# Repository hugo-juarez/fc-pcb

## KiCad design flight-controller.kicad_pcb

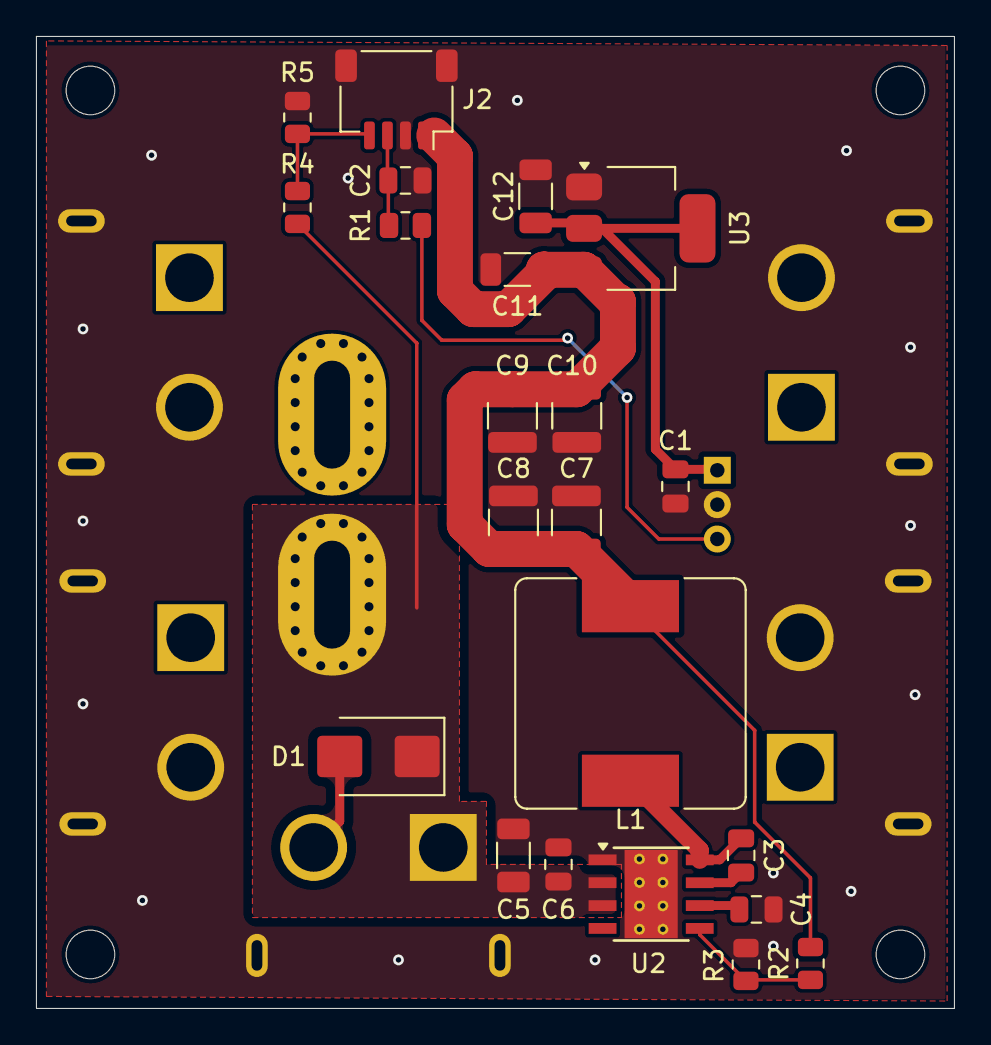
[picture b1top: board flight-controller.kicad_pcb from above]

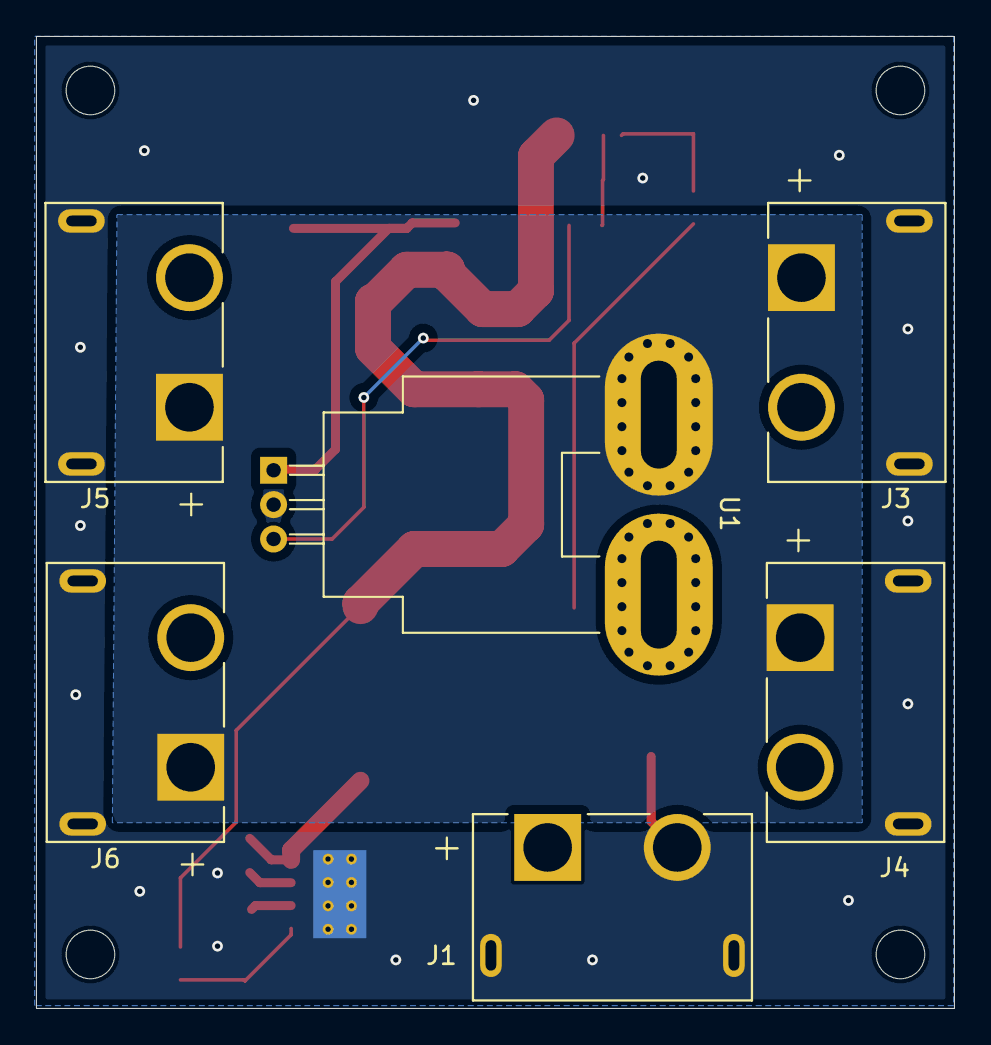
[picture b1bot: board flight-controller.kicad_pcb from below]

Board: 2 copper layers, 51.0 x 54.0 mm, 28 parts (6 on the bottom side), 12 nets.

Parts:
C1, C3: 100nF; C_0805_2012Metric
C2: 10nF; C_0805_2012Metric
C4: 1uF; C_0805_2012Metric
C5, C11, C12: 10uF; C_1206_3216Metric
C6: 220nF; C_0805_2012Metric
C7, C8, C9, C10: 22uF; C_1210_3225Metric
D1: SMBJ18A; D_SMB
J1: XT60PW-M; AMASS_XT60PW-M
J2: SM04B-SRSS-TB; JST_SH_SM04B-SRSS-TB_1x04-1MP_P1.00mm_Horizontal
J3, J4, J5, J6: XT60PW-F; AMASS_XT60PW-F
L1: SRR1260-8R2Y; L_Bourns_SRR1260
R1: 1kΩ; R_0805_2012Metric
R2: 100kΩ; R_0805_2012Metric
R3: 24.9kΩ; R_0805_2012Metric
R4: 10kΩ; R_0805_2012Metric
R5: 2.2kΩ; R_0805_2012Metric
U1: ACS773LCB-100B-PFF; Allegro_CB_PFF
U2: LMR33630ADDA; Texas_HSOP-8-1EP_3.9x4.9mm_P1.27mm_ThermalVias
U3: AMS1117-3.3; SOT-223-3_TabPin2

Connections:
+3.3V: C1.1, C12.1, U1.1 (VCC), U3.2 (VO)
+5V: C7.1, C8.1, C9.1, C10.1, C11.1, J2.1, L1.2, R2.1, U3.3 (VI)
/CURR_SENSE: C2.1, J2.3, R1.1
/VBAT: C5.1, C6.1, D1.1 (K), J1.1, R4.1, U1.4 (IP+), U2.2 (VIN), U2.3 (EN)
/VBAT_SENSE: J2.4, R4.2, R5.1
/VBAT_SW: J3.1, J4.1, J5.1, J6.1, U1.5 (IP-)
GND: C1.2, C2.2, C4.2, C5.2, C6.2, C7.2, C8.2, C9.2, C10.2, C11.2, C12.2, D1.2 (A), J1.2 (N), J1.SH1 (SHIELD), J1.SH2 (SHIELD), J2.2, J2.MP, J3.2 (N), J3.SH1 (SHIELD), J3.SH2 (SHIELD), J4.2 (N), J4.SH1 (SHIELD), J4.SH2 (SHIELD), J5.2 (N), J5.SH1 (SHIELD), J5.SH2 (SHIELD), J6.2 (N), J6.SH1 (SHIELD), J6.SH2 (SHIELD), R3.2, R5.2, U1.2 (GND), U2.1 (GND), U2.9 (GND), U3.1 (GND)
unnamed: R1.2, U1.3 (VIOUT)
unnamed: C3.1, U2.7 (BOOT)
unnamed: R2.2, R3.1, U2.5 (FB)
unnamed: C3.2, L1.1, U2.8 (SW)
unnamed: C4.1, U2.6 (VCC)

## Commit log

2026-03-22 chore: Initialize pcb project with BMI088 symbol
2026-03-22 chore: Modified to remove auto saved files
2026-03-22 feat: Added stm32 header connectors
2026-03-29 feat: Added bmp390 schematic
2026-03-29 fix: Fixed CSB pin style to inverted
2026-03-30 feat: Added bmp390 to main schematic
2026-03-30 feat: Added ACS773 sensor
2026-03-30 feat: Added pinout of BN-088
2026-03-30 feat: Added J_ESC_POWER pins for powering the board
2026-03-30 feat: Added headers of stm32 to schematic
2026-03-30 feat: Added RGB LED
2026-03-30 feat: Added buzzer
2026-03-30 fix: Modified to use connectors to external BEC
2026-03-30 fix: Named of J_ESC_POWER connector
2026-03-31 feat: Added diodes to power inputs
2026-03-31 fix: Added values to bmi and bmp sensors
2026-03-31 feat: Added pcb footprints of bmi088 and bmp390
2026-03-31 chore: Added footprints to elements
2026-03-31 fix: Correct pin 4 of bmp390
2026-03-31 chore: Initialized pcb
2026-03-31 fix: Corrected buzzer footprint
2026-03-31 feat: Placed CN connectors on right location
2026-04-02 chore: Starting from scratch since I will be developing two boards
2026-04-02 chore: Initialized project with XT60PW-M in lib
2026-04-02 feat: Added Battery Connector and TVS diode
2026-04-02 feat: Added ACS773
2026-04-02 feat: Added buck converter
2026-04-02 chore: Assigned footprints to components
2026-04-02 feat: Added LDO
2026-04-02 fix: Fixed low pass filter for curr_sense
2026-04-02 feat: Added voltage divider
2026-04-02 feat: Added ESC connectors
2026-04-02 fix: Fixed correct power input to XT60
2026-04-03 chore: Initialize pcb design
2026-04-03 mend
    chore: Initialize pcb design
2026-04-03 fix: Modified board setup to fit jlcpcb guidelines
2026-04-03 feat: Added high_current net
2026-04-03 fix: Updated right footprint and pcb design
2026-04-03 fix: Added footprint, schematic and 3d model for xt60pw-f
2026-04-03 feat: Updated schematic and pcb to use correct xt60 3d model
2026-04-03 feat: Modified connector to flight controller from power board
2026-04-03 feat: Placed buck converter
2026-04-07 feat: Placed correct location buck converter
2026-04-07 feat: Finished placing AMS
2026-04-07 fix: Fixed DRC errors
2026-04-07 feat: Added VBAT plane
2026-04-07 feat: Added VBAT_SW plane
2026-04-07 feat: Finished routing 5V
2026-04-07 feat: Added 3.3V trace and VBAT_SW
2026-04-07 feat: Routed analog signals
2026-04-07 feat: Added both ground planes
2026-04-07 feat: Added 3d models
2026-04-07 chore: Generated gerber files
2026-04-07 chore: Generated CPL and BOM
2026-04-07 fix: Updated correct L1 part
2026-04-07 chore: Marked DNP components that are going to be hand soldered
2026-04-14 chore: Moved to board1-pdb project
2026-04-14 feat: Added fabrication files for board1-pdb
